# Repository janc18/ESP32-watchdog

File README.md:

# ESP32-watchdog 

This watch will be a multipurpose watch, that will have some kind of Espressif's MCU because it's cheap a come with good features like
Bluetooth and Wi-Fi.

I want to have the more compact design, with that said, the screen and battery define the size watch. 

Searching on Aliexpress I found the next options 

|ID|Technology type|Consumption (mAh) - Voltage (V)|Communication interface|Size|Price|Resolution|
|-|-|-|-|-|-|-|
|1|TFT-LCD|95mAh-5v|UART|47,5mm diameter x 27,0mm de height|371 MX|240px|
|2|Electronic paper screen Monochrome|0.15mAh|-|1.28in|574.29 MX 2 units| 128px|

**I decided to use the next LCD screen**

[Here is the purchase link](https://es.aliexpress.com/item/1005004617618178.html)

**Maybe in the next iteration I will choose for a smaller screen**

## Links
1. https://es.aliexpress.com/item/1005005295747021.html
2. https://es.aliexpress.com/item/1005004555311346.html

## Buttons 
For applications control it is needed to have some kind of inputs, like in common watches,with the hour configured through buttons.
One option is to have capacitive buttons or micro-buttons.

## Capacitive touch sensor
Following this document https://ww1.microchip.com/downloads/en/AppNotes/Capacitive-Touch-Sensor-Design-Guide-DS00002934-B.pdf
This type of sensor touch it seems the best option, it is called "slide sensor", at "Extend Interpolation" form.

## Programming port 
The programming port it will be a micro-usb with the CHG340

## ESP32-S3's power consumption 

|Mode|Power consumption|
|-|-|
|Recommended|500(mA)|
|deep sleep|7-8(uA)|
|light sleep|240(uA)|
|wifi|355mA|

In the case that I want to use Wi-Fi with another application running for three hours on a day and with powered on screen.

## Conceptual design

## First PCB design

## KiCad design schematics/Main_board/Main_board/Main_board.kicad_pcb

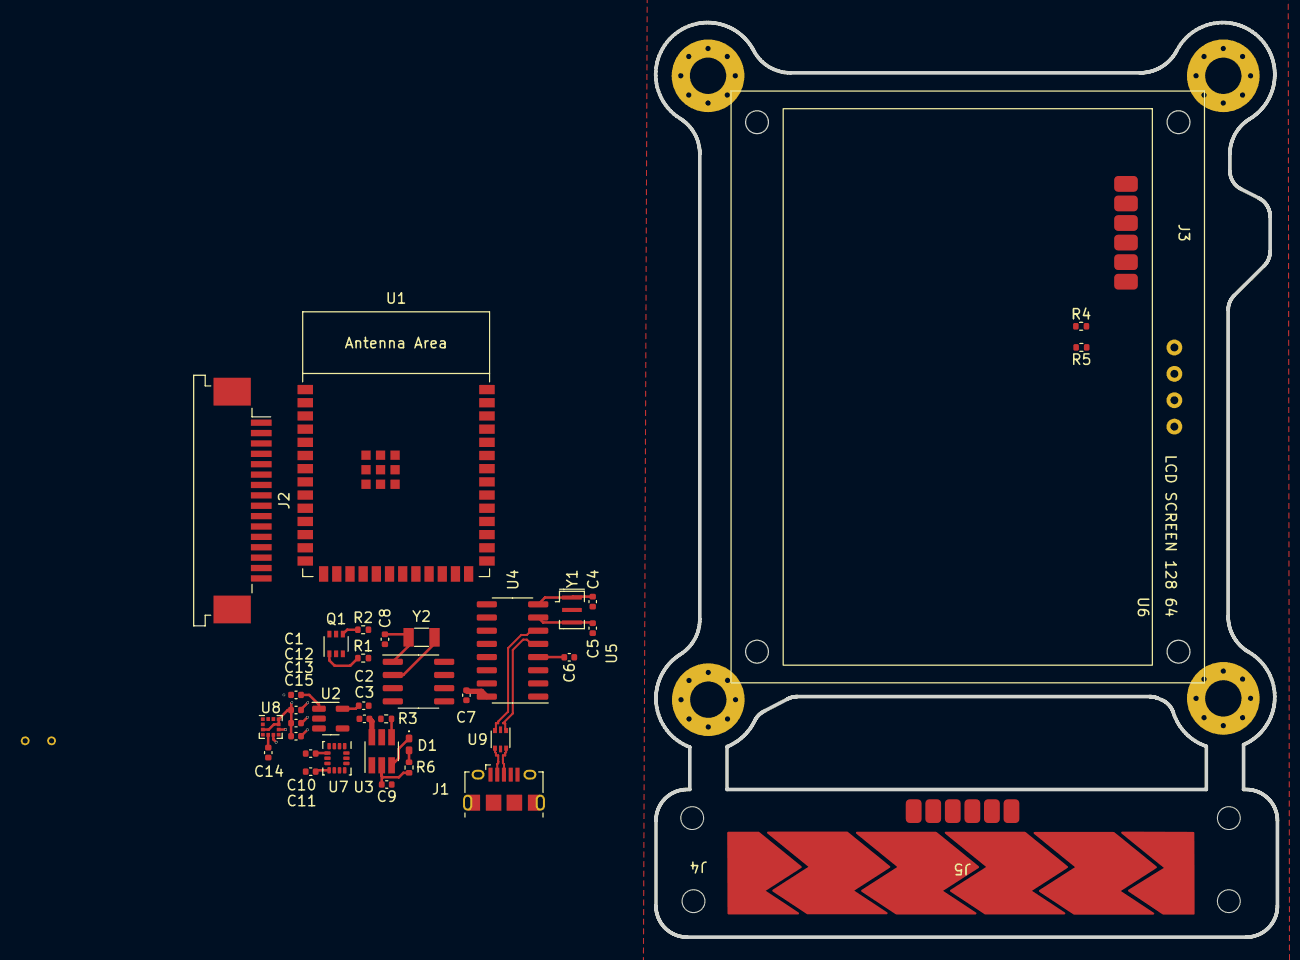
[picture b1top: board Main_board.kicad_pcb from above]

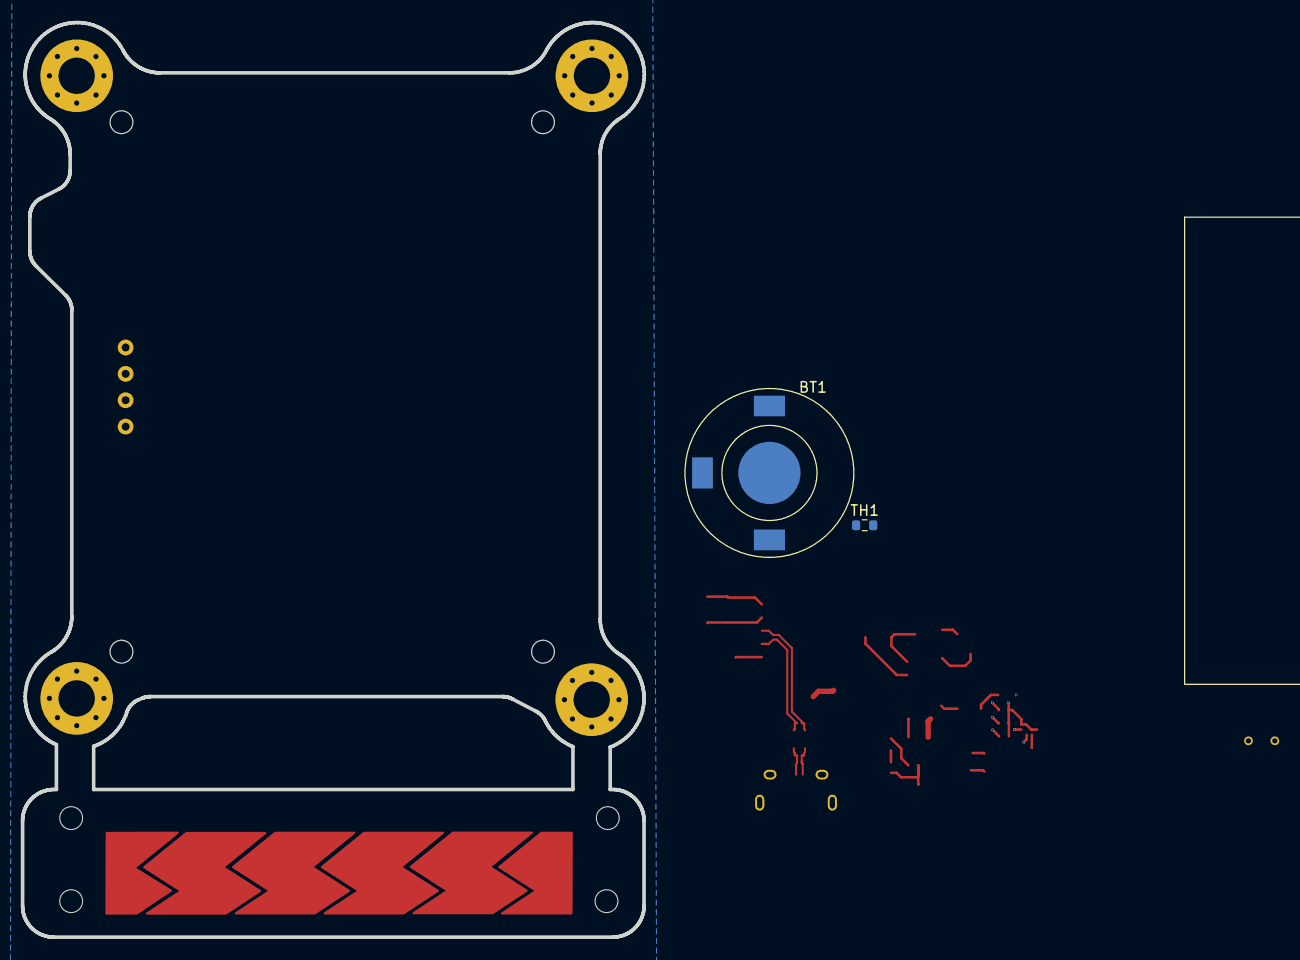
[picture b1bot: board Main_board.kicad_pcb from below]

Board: 4 copper layers, 59.9 x 88.1 mm, 50 parts (3 on the bottom side), 50 nets.

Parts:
BT1: 1v5 LR44; MY-LR44-02
BT2: 3v7 LIpo; lipo_battery_800mA
C1, C2, C3, C9: 1uf; C_0402_1005Metric
C4, C5: 33p; C_0402_1005Metric
C6, C7: 0.1u; C_0402_1005Metric
C8: 22p; C_0402_1005Metric
C10, C11, C12, C13: 100nf; C_0402_1005Metric
C14: 220nf; C_0402_1005Metric
C15: 10uf; C_0402_1005Metric
D1: LED; LED_0402_1005Metric_Pad0.77x0.64mm_HandSolder
H1, H2, H3, H4: MountingHole; MountingHole_3.5mm_Pad_Via
H5, H6, H7, H8: MountingHole; MountingHole_2.2mm_M2_DIN965
J1: USB_B_Micro; USB_Micro-B_Amphenol_10118194_Horizontal
J2: Conn_01x16_Female; TE_1-84953-6_1x16-1MP_P1.0mm_Horizontal
J3, J5: Conn_01x06_Female; slider_sensors_points_smd
J4: Conn_01x06_Female; slide_sensor_6p
Q1: UMH3N; SOT-363_SC-70-6
R1, R3: 1K; R_0402_1005Metric
R2: 10k; R_0402_1005Metric
R4, R5: 4k7; R_0402_1005Metric
R6: 1k5; R_0402_1005Metric
TH1: NCP18XH103F03RB; R_0603_1608Metric
U1: ESP32-S3-WROOM-1
U2: AP2112K-3.3; SOT-23-5
U3: bq21040; SOT-23-6_Handsoldering
U4: CH340G; SOIC-16_3.9x9.9mm_P1.27mm
U5: PCF8563T; SOIC-8_3.9x4.9mm_P1.27mm
U6: LCD; LCD_IIC_12864
U7: LSM6DS3; LGA-14_3x2.5mm_P0.5mm_LayoutBorder3x4y
U8: LIS2MDL; LGA-12_2x2mm_P0.5mm
U9: USBLC6-2P6; SOT-666
Y1: Crystal_GND2_Small; Resonator_SMD_Murata_CSTxExxV-3Pin_3.0x1.1mm
Y2: 32.768kHz; Crystal_SMD_3215-2Pin_3.2x1.5mm

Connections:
+3V3: C2.1, C10.1, C11.2, C12.1, C13.1, C15.1, J2.1, J2.2, Q1.3 (C2), Q1.6 (C1), R4.2, R5.1, U2.5 (VOUT), U6.4 (Vcc), U7.5 (VDDIO), U7.8 (VDD), U7.12 (CS), U8.3 (~CS), U8.9 (Vdd), U8.10 (Vdd_IO)
+5V: C3.2, C7.1, U3.6 (VIN), U4.16 (VCC), U9.2 (GND)
+BATT: BT2.1 (+), C1.1, C9.2, R6.2, U2.1 (VIN), U2.3 (EN), U3.2 (VOUT)
/BOOT0: R1.2, U1.27 (GPIO0/BOOT)
/Connectors/D_ESD+: J1.3 (D+), U9.6 (I/O1)
/Connectors/D_ESD-: J1.2 (D-), U9.4 (I/O2)
/D+: U4.5 (UD+), U9.1 (I/O1)
/D-: U4.6 (UD-), U9.3 (I/O2)
/DTR: Q1.5 (B2), U4.13 (~DTR)
/EN: R2.2, U1.3 (EN)
/I/O_1: J2.3, U1.39 (GPIO1/TOUCH1/ADC1_CH0)
/I/O_2: J2.4, U1.38 (GPIO2/TOUCH2/ADC1_CH1)
/I/O_3: J2.5, U1.15 (GPIO3/TOUCH3/ADC1_CH2)
/I/O_4: J2.6, U1.4 (GPIO4/TOUCH4/ADC1_CH3)
/I/O_5: J2.7, U1.5 (GPIO5/TOUCH5/ADC1_CH4)
/MISO: J2.13, U1.21 (GPIO13/TOUCH13/ADC2_CH2/FSPIQ/FSPIIO7/S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)
/MOSI: J2.12, U1.19 (GPIO11/TOUCH11/ADC2_CH0/FSPID/FSPIIO5/S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)
/RTS: Q1.2 (B1), U4.14 (~RTS)
/SCL_1: J2.11, R4.1, U1.23 (GPIO21), U5.5 (SDA), U6.1 (SDA), U7.14 (SDA), U8.4 (SDA/SDI/SDO)
/SDA_1: J2.10, R5.2, U1.26 (GPIO45), U5.6 (SCL), U6.2 (SCL), U7.13 (SCL), U8.1 (SCL/SPC)
/SPI_CLK: J2.14, U1.20 (GPIO12/TOUCH12/ADC2_CH1/FSPICLK/FSPIIO6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)
/TOUCH_1: J3.1, U1.6 (GPIO6/TOUCH6/ADC1_CH5)
/TOUCH_2: J3.2, U1.7 (GPIO7/TOUCH7/ADC1_CH6)
/TOUCH_3: J3.3, U1.12 (GPIO8/TOUCH8/ADC1_CH7/SUBSPICS1)
/TOUCH_4: J3.4, U1.17 (GPIO9/TOUCH9/ADC1_CH8/FSPIHD/SUBSPIHD)
/TOUCH_5: J3.5, U1.18 (GPIO10/TOUCH10/ADC1_CH9/FSPICS0/FSPIIO4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)
/TOUCH_6: J3.6, U1.22 (GPIO14/TOUCH14/ADC2_CH3/FSPIWP/FSPIDQS/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)
/UART_RX0_PGR: J2.9, U1.37 (U0TXD/GPIO43/CLK_OUT1), U4.3 (RXD)
/UART_TX0_PGR: J2.8, U1.36 (U0RXD/GPIO44/CLK_OUT2), U4.2 (TXD)
GNDREF: BT1.2 (-), BT2.2 (-), C1.2, C2.2, C3.1, C4.2, C5.2, C6.1, C7.2, C8.2, C9.1, C10.2, C11.1, C12.2, C13.2, C14.2, C15.2, J1.4 (ID), J1.5 (GND), J1.6 (Shield), J2.15, J2.16, R3.2, TH1.2, U1.1 (GND), U1.40 (GND), U1.41 (GND), U2.2 (GND), U3.5 (GND), U4.1 (GND), U5.4 (VSS), U6.3 (GND), U7.1 (SDO/SA0), U7.2 (SDX), U7.3 (SCX), U7.6 (GND), U7.7 (GND), U8.6 (GND), U8.8 (GND), Y1.2
unnamed: BT1.1 (+), U5.8 (VDD)
unnamed: D1.2 (A), R6.1
unnamed: D1.1 (K), U3.3 (CHR)
unnamed: J4.1, J5.1
unnamed: J4.2, J5.2
unnamed: J4.3, J5.3
unnamed: J4.4, J5.4
unnamed: J4.5, J5.5
unnamed: J4.6, J5.6
unnamed: Q1.1 (E1), R1.1
unnamed: Q1.4 (E2), R2.1
unnamed: R3.1, U3.4 (ISET)
unnamed: TH1.1, U3.1 (TS)
unnamed: C6.2, U4.4 (V3)
unnamed: C5.1, U4.7 (XI), Y1.3
unnamed: C4.1, U4.8 (XO), Y1.1
unnamed: C8.1, U5.1 (OSCI), Y2.1
unnamed: U5.2 (OSCO), Y2.2
unnamed: C14.1, U8.5 (C1)
VBUS: J1.1 (VBUS), U9.5 (VBUS)

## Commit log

2023-04-02 add: English Translation to README file
2023-04-03 remove: Circuit block diagram
2023-05-05 Add: Conceptual design images
2023-05-05 Update: added conceptual design image to README file
2023-05-05 Add: Kicad schematics files
2023-05-05 Add: Slider_sensor_board Kicad schematics files
2023-05-05 Update:added new rule of kicad backups
2023-05-09 Update: Added symbols and footprints
2023-05-09 Update: Added new rule to gitignore
2023-05-09 Update: Added LCD symbol
2023-05-09 Add: Creation of 3d file (FCStd an STEP)
2023-05-09 Add: Creation of schematic and footprint
2023-05-09 Update: added FCstd1 rule to gitignore
2023-05-10 Add: Battery holder 3D design STEP and FCStd
2023-05-10 Add: LiPo battery 3D design STEP and FCStd
2023-05-10 Add: Battery holder footprint
2023-05-10 Update: added new schematics components
2023-05-15 Add: footprint for slide sensor
2023-05-15 Update: add components to schematics
2023-05-20 Add: BOM file
2023-05-20 Update: added datasheet to KiCad component
2023-05-23 Add: empthy flutter project
2023-05-23 Update: added new rules for flutter app
2023-05-23 Update: added a new field for kicad components for the #lcsc part
2023-05-23 delete: slider sensor board because it will be include in the main board
2023-06-05 Add: Label sticker with all the connections(i/o,uart,spi and i2c)
2023-06-05 Add: Watch Blender render image
2023-06-05 Update: First pcb revision complete
2023-06-05 Add: designs for 3d parts and footprints
2023-06-05 Add: Main bord images
2023-06-05 Add: layout to do the cuts in kicad
2023-06-05 Update: change colors
2023-06-05 Add: FreeCad case file and stl files
2023-06-05 Update: added new rule for backups kicad's files
2023-06-06 Add: lcd screen image
2023-06-06 Update: README with new information, abouat the new screen chosen
2023-09-10 update: to kicad version 7, and arrange all the components on their respective hierarchy page
2023-09-10 fix: 3d step file paths
2023-09-14 update: All the resistors and capacitors footprints changed from 0603 to 0402
